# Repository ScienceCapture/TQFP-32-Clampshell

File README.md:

# TQFP-32-Clampshell
Clampshell is a device used for programming SMD packaged integrated circuits. It makes a connection to all the pins without the need for soldering. This particular design can program TQFP-32 IC packages and is designed for the ATMega328-P (Arduino MCU) chip. It has a USB-C connector for power, an integrated LED to run the blink sketch after programming and features an ISP connector for AVR programming (I used POLOLU-3172 AVR programmer). This PCB also provides access to all the 32 individual pins of the IC using pin headers. The clampshell module is QFP32-0.5-CP01N and it can be bought off the internet (I used AliExpress).

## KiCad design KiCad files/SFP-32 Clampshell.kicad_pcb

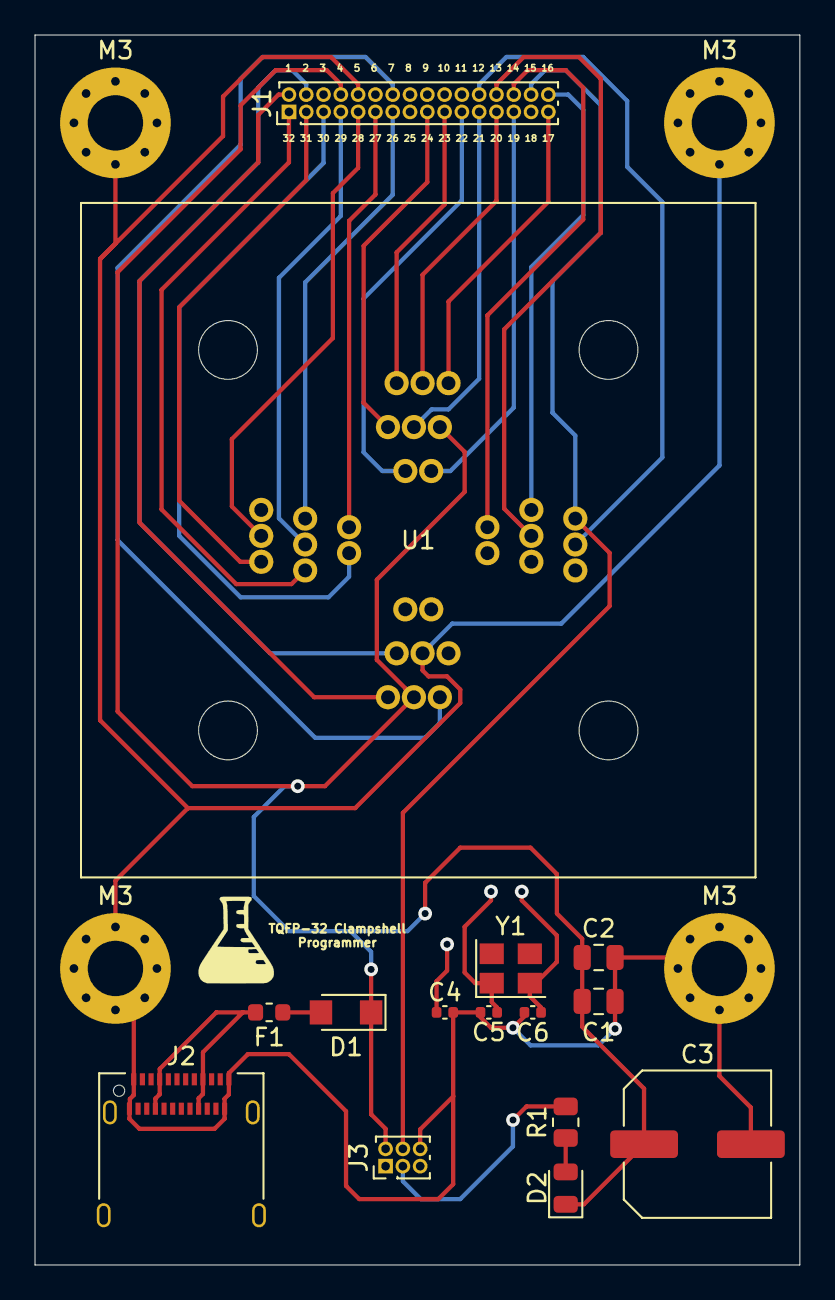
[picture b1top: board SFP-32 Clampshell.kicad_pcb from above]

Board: 4 copper layers, 44.2 x 71.1 mm, 19 parts (0 on the bottom side), 34 nets.

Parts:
C1, C2: 1uF; C_0805_2012Metric
C3: 10uF; C_Elec_8x6.2
C4: 100nF; C_0402_1005Metric
C5, C6: 22pF; C_0402_1005Metric
D1: SS1P3L; D_SMF
D2: LED; LED_0805_2012Metric
F1: MFFSMF050; Fuse_0603_1608Metric
J1: Conn_02x16_Odd_Even; PinHeader_2x16_P1.00mm_Vertical
J2: USB_C_Receptacle_USB2.0; USB_C_Receptacle_Amphenol_12401610E4-2A
J3: Conn_02x03_Top_Bottom; PinHeader_2x03_P1.00mm_Vertical
M3, M3#2, M3#3, M3#4: MountingHole_3.2mm_M3_Pad_Via
R1: 1k; R_0805_2012Metric
U1: SPF-32_Clampshell_Symbol; SPF-32_Clampshell_Footprint
Y1: 16MHz; Crystal_SMD_3225-4Pin_3.2x2.5mm

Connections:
1: J1.2, U1.1
2: J1.4, U1.2
3: J1.6, U1.3
5: C1.2, C2.2, C3.2, C4.2, C5.1, C6.2, J1.10, J2.A1, J2.A12, J2.B1, J2.B12, J3.6, M3.1, M3#2.1, M3#3.1, M3#4.1, U1.5
6: J1.12, U1.6
7: C5.2, J1.14, U1.7, Y1.1
8: C6.1, J1.16, U1.8, Y1.2
9: J1.18, U1.9
10: J1.20, U1.10
11: J1.22, U1.11
12: J1.24, U1.12
13: J1.26, U1.13
14: J1.28, U1.14
15: J1.30, J3.4, U1.15
16: J1.32, J3.1, U1.16
17: J1.31, J3.3, R1.2, U1.17
18: C1.1, C2.1, C3.1, D1.1, D2.1, J1.8, J1.29, J3.2, U1.4, U1.18
19: J1.27, U1.19
20: C4.1, J1.25, U1.20
21: J1.23, U1.21
22: J1.21, U1.22
23: J1.19, U1.23
24: J1.17, U1.24
25: J1.15, U1.25
26: J1.13, U1.26
27: J1.11, U1.27
28: J1.9, U1.28
29: J1.7, J3.5, U1.29
30: J1.5, U1.30
31: J1.3, U1.31
32: J1.1, U1.32
unnamed: D1.2, F1.1
unnamed: D2.2, R1.1
unnamed: F1.2, J2.A4, J2.A9, J2.B4, J2.B9
